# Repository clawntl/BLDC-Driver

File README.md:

# BLDC-Driver: a compact FOC driver board

BLDC-Driver is an integrated brushless motor driver built around an **STM32G431** microcontroller and a **TI DRV8316** three-phase gate driver with integrated MOSFETs. It runs field-oriented control (FOC) with [SimpleFOC](https://github.com/simplefoc) and takes current (torque) commands over CAN. It suits gimbal motors and small direct-drive wheels.

The board includes an optional **AS5048A** magnetic encoder on a break-away tab. With the tab removed, the board measures just **39 mm × 36 mm**.

## Features

| | |
|---|---|
| **MCU** | STM32G431CBU6 (Cortex-M4F, 170 MHz max, run at 160 MHz; CORDIC used for fast trig) |
| **Power stage** | DRV8316 with integrated FETs: 3 A continuous / 8 A peak, 6-PWM control over SPI |
| **Supply** | 5–35 V DC. The DRV8316 buck converter generates 5 V, and an XC6206 LDO generates 3.3 V |
| **Current sense** | DRV8316 integrated low-side current-sense amplifiers on all three phases |
| **Position sensor** | AS5048A 14-bit magnetic encoder (SPI1) on a break-away tab, or an external sensor via the SPI1 header |
| **Communication** | CAN via a TJA1051T/3 transceiver (FDCAN capable up to 5 Mbit/s; the firmware uses 1 Mbit/s classic CAN). Two JST-PH connectors allow daisy-chaining |
| **CAN termination** | Optional split 120 Ω termination, set with two jumpers |
| **Other I/O** | USB-C (CDC serial console + DFU flashing), SWD header, SPI3 header, user button, user LED, power LED |
| **Supply sensing** | 100 kΩ / 10 kΩ divider on VIN, read by the MCU (PA3) |
| **Mounting** | 4 × M2 holes, 33 mm × 30 mm spacing |

## Repository layout

| Path | Contents |
|---|---|
| [`Hardware/`](Hardware) | KiCad project for the v0.2 board (schematic, PCB, custom footprints and symbols) |
| [`Hardware/production/`](Hardware/production) | Fabrication outputs: Gerber zip, BOM and pick-and-place files (JLCPCB/LCSC part numbers) |
| [`schematic_v0.2.pdf`](schematic_v0.2.pdf) | PDF export of the schematic |
| [`Firmware/`](Firmware) | PlatformIO firmware: the CAN motor driver and a bench-test build |
| [`Images/`](Images) | Pinout diagram |
| [`docs/`](docs) | Detailed documentation (see below) |

## Documentation

- **[Hardware guide](docs/hardware.md)**: pin mapping, connectors, jumpers, buttons, LEDs and manufacturing notes.
- **[Firmware guide](docs/firmware.md)**: building, flashing, first-time configuration, the serial console, tuning parameters and the bench-test firmware.
- **[Test routines](docs/test-routines.md)**: step-by-step bench testing of a board, motor and encoder with the `motor_test` firmware, with expected readings and troubleshooting.
- **[CAN protocol](docs/can-protocol.md)**: message IDs, frame formats, status and error codes, plus an example host program.

## Quick start

1. **Install [PlatformIO](https://platformio.org/)** (the VS Code extension or the CLI).
2. **Put the board in DFU mode.** Hold **BOOT**, plug in USB-C (or tap **RST**), then release **BOOT**. On a board that's already running the firmware, you can type `dfu` in the serial console instead.
3. **Build and flash** from the `Firmware/` directory:
   ```bash
   cd Firmware
   ```
   ```bash
   pio run -e driver -t upload
   ```
4. **Configure the board** over USB serial. The board boots unconfigured, with CAN disabled:
   ```bash
   pio device monitor
   ```
   Then type:
   ```text
   set side left      # or: set side right  (selects the CAN IDs)
   set invert off     # optional: flip the sign of commands/telemetry for a mirrored motor
   save               # writes to flash and reboots
   ```
5. **Drive it over CAN** at 1 Mbit/s:
   - Send `0x10` to the board's command ID (`0x021` left / `0x022` right) to align and start FOC.
   - Wait for the `[0x10][1.0f]` reply.
   - Stream target currents in amps as two big-endian floats on ID `0x020` at least every 100 ms.

   See [docs/can-protocol.md](docs/can-protocol.md) for the full protocol.

> [!CAUTION]
> Test new motors with the wheels off the ground and a current-limited supply. The `motor_test` bench firmware ([docs/firmware.md](docs/firmware.md#bench-test-firmware-motor_test)) checks the encoder, power stage and current sense step by step before you run closed-loop control.

## Status

This is hardware revision **v0.2**. The firmware's default motor parameters (11 pole pairs, 2 A current limit, 10 V voltage limit) live in [`Firmware/include/motor_config.h`](Firmware/include/motor_config.h). Change them to match your motor.

## License

This project is shared under the terms of the [GNU Affero General Public License Version 3](https://choosealicense.com/licenses/agpl-3.0/) as published by the Free Software Foundation.

The bundled [`ACANFD_STM32_G431`](Firmware/lib/ACANFD_STM32_G431) library is a stripped-down fork of Pierre Molinaro's [ACANFD-STM32](https://github.com/pierremolinaro/acanfd-stm32) and keeps its own MIT license.

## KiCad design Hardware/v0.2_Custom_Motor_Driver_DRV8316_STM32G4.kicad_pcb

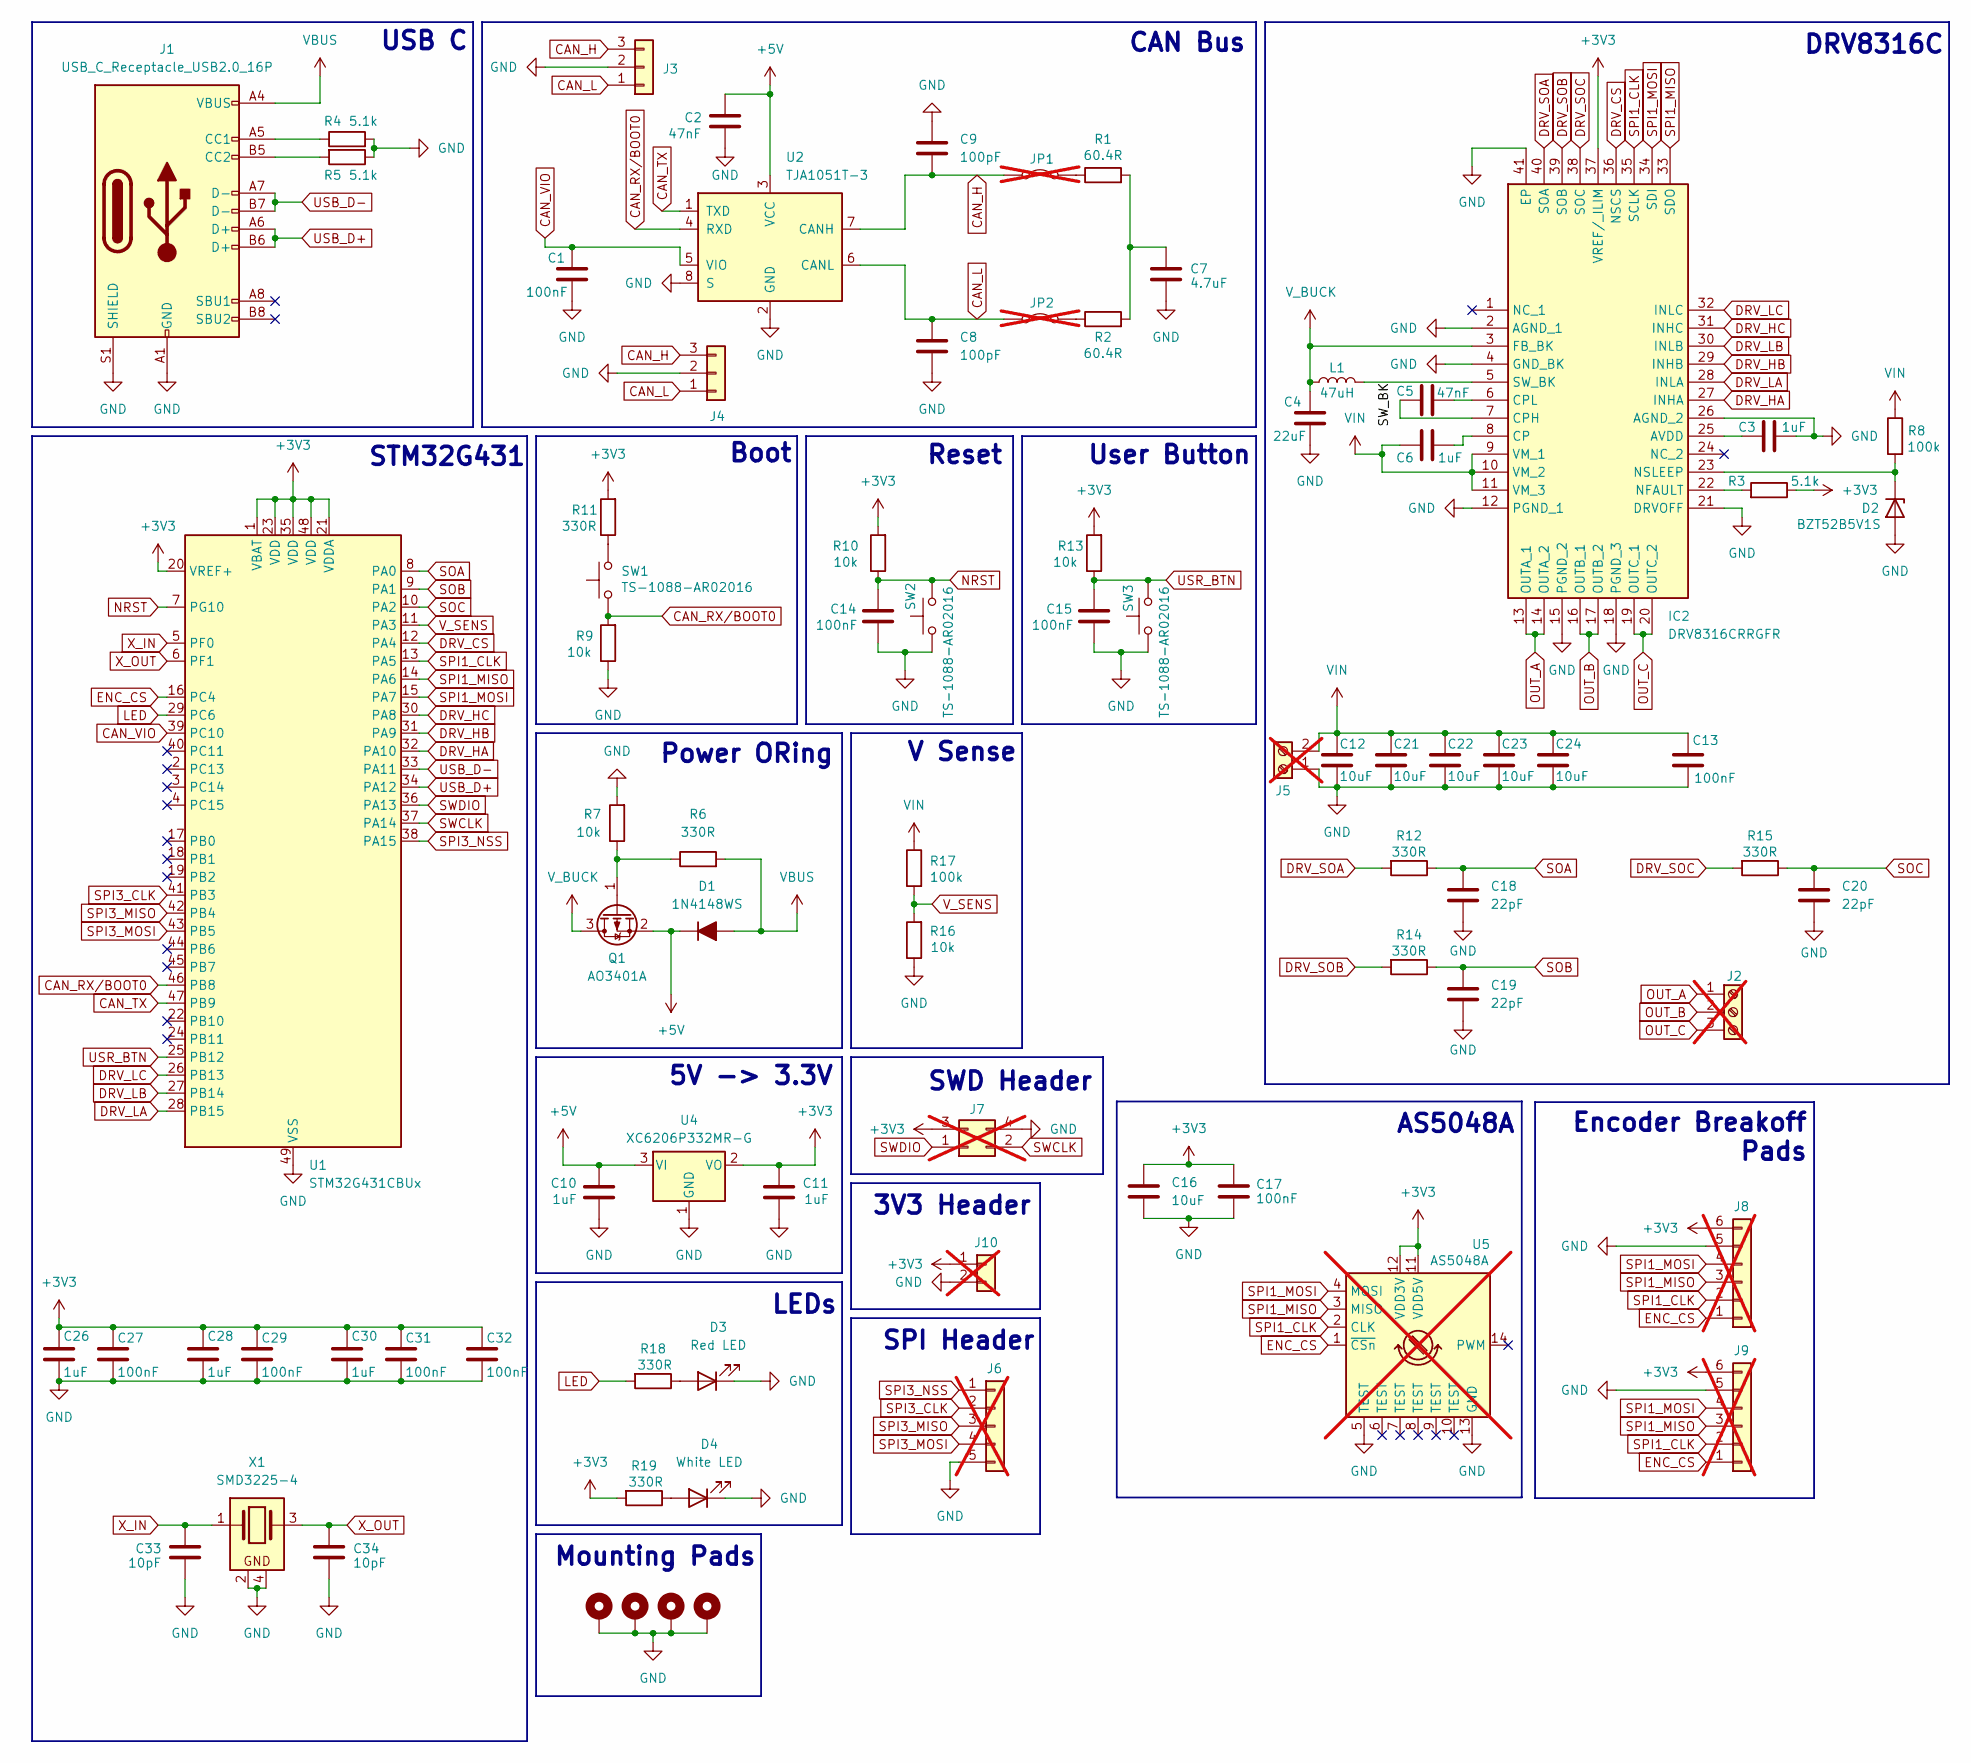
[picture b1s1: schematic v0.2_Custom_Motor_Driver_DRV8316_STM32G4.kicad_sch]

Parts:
C1, C13, C14, C15, C17, C27, C29, C31, C32: 100nF; C_0402_1005Metric; LCSC C307331
C2, C5: 47nF; C_0603_1608Metric; LCSC C1622
C3, C6, C10, C11, C26, C28, C30: 1uF; C_0402_1005Metric; LCSC C52923
C4: 22uF; C_0603_1608Metric; LCSC C59461
C7: 4.7uF; C_0805_2012Metric; LCSC C1779
C8, C9: 100pF; C_0402_1005Metric; LCSC C1546
C12, C21, C22, C23, C24: 10uF; C_0805_2012Metric; LCSC C440198
C16: 10uF; C_0603_1608Metric; LCSC C96446
C18, C19, C20: 22pF; C_0402_1005Metric; LCSC C1555
C33, C34: 10pF; C_0402_1005Metric; LCSC C32949
D1: 1N4148WS; D_SOD-323; LCSC C2128
D2: BZT52B5V1S; D_SOD-323_Zener; LCSC C19077434
D3: Red LED; LED_0603_1608Metric; LCSC C2286
D4: White LED; LED_0603_1608Metric; LCSC C2290
H1, H2, H3, H4: MountingHole_Pad; MountingHole_2.2mm_M2_Pad_Via
IC2: DRV8316CRRGFR; QFN50P500X700X100-41N-D; LCSC C5447274
J1: USB_C_Receptacle_USB2.0_16P; USB_C_Receptacle_GCT_USB4105-xx-A_16P_TopMnt_Horizontal; LCSC C393939
J2: Screw_Terminal_01x03; TerminalBlock_Xinya_XY308-2.54-3P_1x03_P2.54mm_Horizontal; not fitted
J3, J4: Conn_01x03; JST_PH_S3B-PH-K_1x03_P2.00mm_Horizontal; LCSC C157929
J5: Screw_Terminal_01x02; TerminalBlock_MaiXu_MX126-5.0-02P_1x02_P5.00mm; LCSC C3018698; not fitted
J6: Conn_01x05; PinHeader_1x05_P2.54mm_Vertical; not fitted
J7: Conn_02x02_Odd_Even; DebugHeader2x02_P1.27mm; not fitted
J8, J9: Conn_01x06; JST_PH_S6B-PH-K_1x06_P2.00mm_Horizontal Breakoff; not fitted
J10: Conn_01x02; PinHeader_1x02_P2.54mm_Vertical SLIM; not fitted
JP1, JP2: Jumper_2_Bridged; PinHeader_1x02_P2.54mm_Vertical; not fitted
L1: 47uH; L_Changjiang_FNR3015S; LCSC C96151
Q1: AO3401A; SOT-23; LCSC C15127
R1, R2: 60.4R; R_0805_2012Metric; LCSC C72998
R3, R4, R5: 5.1k; R_0402_1005Metric; LCSC C25905
R6, R11, R12, R14, R15, R18, R19: 330R; R_0402_1005Metric; LCSC C25104
R7, R9, R10, R13, R16: 10k; R_0402_1005Metric; LCSC C25744
R8, R17: 100k; R_0402_1005Metric; LCSC C25741
SW1, SW2, SW3: TS-1088-AR02016; LCSC C720477
U1: STM32G431CBUx; QFN-48-1EP_7x7mm_P0.5mm_EP5.6x5.6mm; LCSC C529356
U2: TJA1051T-3; SOIC-8_3.9x4.9mm_P1.27mm; LCSC C38695
U4: XC6206P332MR-G; SOT-23-3; LCSC C5446
U5: AS5048A; TSSOP-14_4.4x5mm_P0.65mm; not fitted
X1: SMD3225-4; Crystal_SMD_3225-4Pin_3.2x2.5mm; LCSC C13738

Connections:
+3V3: C11.2, C16.1, C17.1, C26.1, C27.1, C28.1, C29.1, C30.1, C31.1, C32.1, IC2.37 (VREF/_ILIM), J7.3, J8.6, J9.6, J10.1, R3.2, R10.2, R11.2, R13.2, R19.2, U1.1 (VBAT), U1.20 (VREF+), U1.21 (VDDA), U1.23 (VDD), U1.35 (VDD), U1.48 (VDD), U4.2 (VO), U5.11 (VDD5V), U5.12 (VDD3V)
+5V: C2.1, C10.2, D1.1 (K), Q1.2 (S), U2.3 (VCC), U4.3 (VI)
/SW_BK: IC2.5 (SW_BK), L1.2
CAN_H: C9.2, J3.3, J4.3, JP1.1 (A), U2.7 (CANH)
CAN_L: C8.1, J3.1, J4.1, JP2.1 (A), U2.6 (CANL)
CAN_RX/BOOT0: R9.2, SW1.1, U1.46 (PB8), U2.4 (RXD)
CAN_TX: U1.47 (PB9), U2.1 (TXD)
CAN_VIO: C1.1, U1.39 (PC10), U2.5 (VIO)
DRV_CS: IC2.36 (NSCS), U1.12 (PA4)
DRV_HA: IC2.27 (INHA), U1.32 (PA10)
DRV_HB: IC2.29 (INHB), U1.31 (PA9)
DRV_HC: IC2.31 (INHC), U1.30 (PA8)
DRV_LA: IC2.28 (INLA), U1.28 (PB15)
DRV_LB: IC2.30 (INLB), U1.27 (PB14)
DRV_LC: IC2.32 (INLC), U1.26 (PB13)
DRV_SOA: IC2.40 (SOA), R12.2
DRV_SOB: IC2.39 (SOB), R14.2
DRV_SOC: IC2.38 (SOC), R15.2
ENC_CS: J8.1, J9.1, U1.16 (PC4), U5.1 (~CSn)
GND: C1.2, C2.2, C3.2, C4.2, C7.2, C8.2, C9.1, C10.1, C11.1, C12.2, C13.2, C14.2, C15.2, C16.2, C17.2, C18.2, C19.2, C20.2, C21.2, C22.2, C23.2, C24.2, C26.2, C27.2, C28.2, C29.2, C30.2, C31.2, C32.2, C33.2, C34.2, D2.2 (A), D3.1 (K), D4.1 (K), H1.1, H2.1, H3.1, H4.1, IC2.2 (AGND_1), IC2.4 (GND_BK), IC2.12 (PGND_1), IC2.15 (PGND_2), IC2.18 (PGND_3), IC2.21 (DRVOFF), IC2.26 (AGND_2), IC2.41 (EP), J1.A1 (GND), J1.A12 (GND), J1.B1 (GND), J1.B12 (GND), J1.S1 (SHIELD), J3.2, J4.2, J5.1, J6.5, J7.4, J8.5, J9.5, J10.2, R4.2, R5.1, R7.2, R9.1, R16.1, SW2.1, SW3.1, U1.49 (VSS), U2.2 (GND), U2.8 (S), U4.1 (GND), U5.5 (TEST), U5.13 (GND), X1.2, X1.4
LED: R18.2, U1.29 (PC6)
NRST: C14.1, R10.1, SW2.2, U1.7 (PG10)
unnamed: C7.1, R1.2, R2.2
unnamed: D2.1 (K), IC2.23 (NSLEEP), R8.1
unnamed: D3.2 (A), R18.1
unnamed: D4.2 (A), R19.1
unnamed: C3.1, IC2.25 (AVDD)
unnamed: C6.2, IC2.8 (CP)
unnamed: C5.1, IC2.7 (CPH)
unnamed: C5.2, IC2.6 (CPL)
unnamed: IC2.22 (NFAULT), R3.1
unnamed: J1.A5 (CC1), R4.1
unnamed: J1.B5 (CC2), R5.2
unnamed: JP1.2 (B), R1.1
unnamed: JP2.2 (B), R2.1
unnamed: Q1.1 (G), R6.1, R7.1
unnamed: R11.1, SW1.2
OUT_A: IC2.13 (OUTA_1), IC2.14 (OUTA_2), J2.1
OUT_B: IC2.16 (OUTB_1), IC2.17 (OUTB_2), J2.2
OUT_C: IC2.19 (OUTC_1), IC2.20 (OUTC_2), J2.3
SOA: C18.1, R12.1, U1.8 (PA0)
SOB: C19.1, R14.1, U1.9 (PA1)
SOC: C20.1, R15.1, U1.10 (PA2)
SPI1_CLK: IC2.35 (SCLK), J8.2, J9.2, U1.13 (PA5), U5.2 (CLK)
SPI1_MISO: IC2.33 (SDO), J8.3, J9.3, U1.14 (PA6), U5.3 (MISO)
SPI1_MOSI: IC2.34 (SDI), J8.4, J9.4, U1.15 (PA7), U5.4 (MOSI)
SPI3_CLK: J6.2, U1.41 (PB3)
SPI3_MISO: J6.3, U1.42 (PB4)
SPI3_MOSI: J6.4, U1.43 (PB5)
SPI3_NSS: J6.1, U1.38 (PA15)
SWCLK: J7.2, U1.37 (PA14)
SWDIO: J7.1, U1.36 (PA13)
USB_D+: J1.A6 (D+), J1.B6 (D+), U1.34 (PA12)
USB_D-: J1.A7 (D-), J1.B7 (D-), U1.33 (PA11)
USR_BTN: C15.1, R13.1, SW3.2, U1.25 (PB12)
VBUS: D1.2 (A), J1.A4 (VBUS), J1.A9 (VBUS), J1.B4 (VBUS), J1.B9 (VBUS), R6.2
VIN: C6.1, C12.1, C13.1, C21.1, C22.1, C23.1, C24.1, IC2.9 (VM_1), IC2.10 (VM_2), IC2.11 (VM_3), J5.2, R8.2, R17.2
V_BUCK: C4.1, IC2.3 (FB_BK), L1.1, Q1.3 (D)
V_SENS: R16.2, R17.1, U1.11 (PA3)
X_IN: C33.1, U1.5 (PF0), X1.1
X_OUT: C34.1, U1.6 (PF1), X1.3

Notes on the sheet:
Power ORing
LEDs
5V -> 3.3V
V Sense
USB C
AS5048A
SWD Header
CAN Bus
SPI Header
STM32G431
Encoder Breakoff Pads
DRV8316C
Reset
3V3 Header
Mounting Pads
User Button
Boot

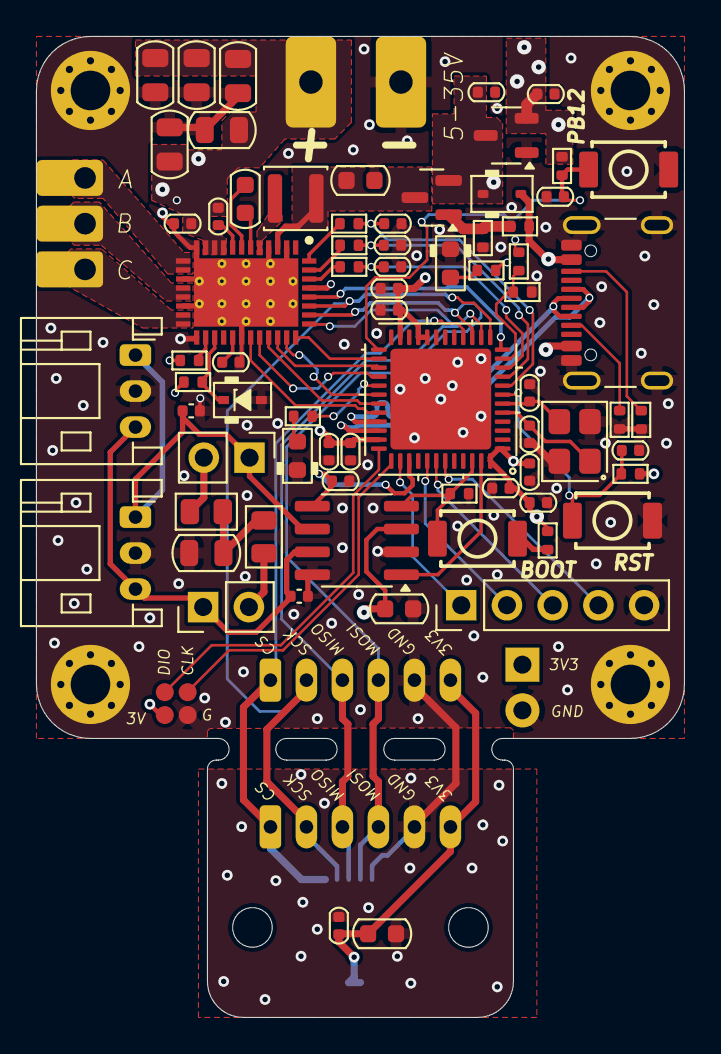
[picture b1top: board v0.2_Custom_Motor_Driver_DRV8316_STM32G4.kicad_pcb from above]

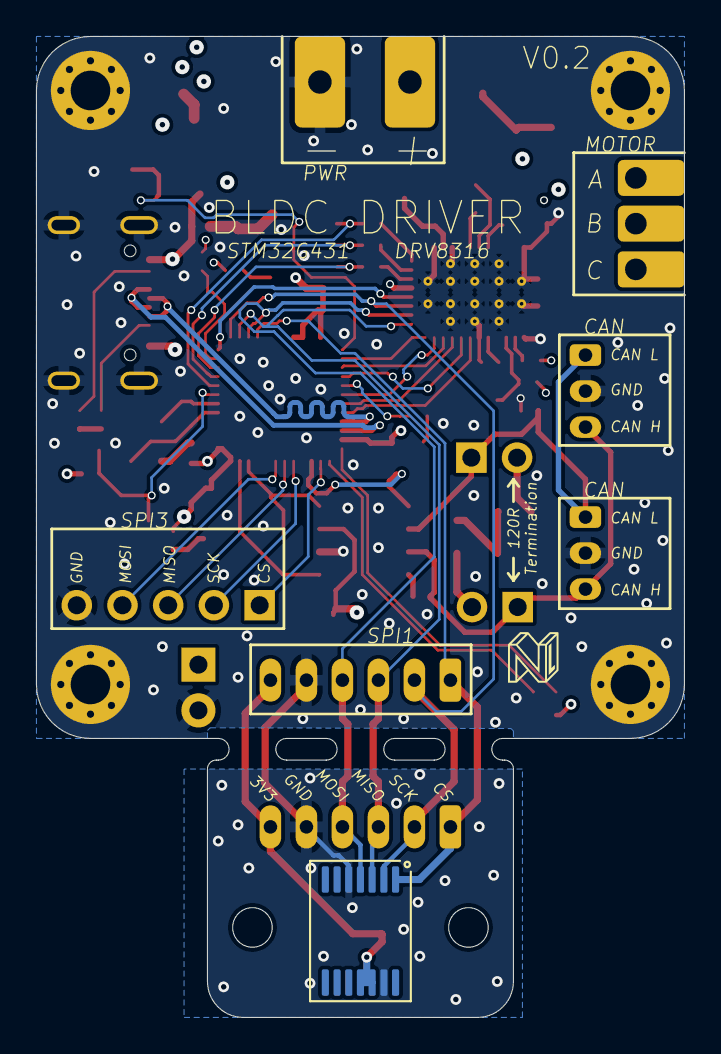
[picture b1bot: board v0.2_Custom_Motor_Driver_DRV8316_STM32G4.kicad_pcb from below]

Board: 4 copper layers, 36.0 x 54.5 mm, 83 parts (2 on the bottom side), 61 nets.

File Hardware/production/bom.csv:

Designator,Footprint,Quantity,Value,LCSC Part #
"C1, C13, C14, C15, C17, C27, C29, C31, C32",0402,9,100nF,C307331
"C10, C11, C26, C28, C3, C30, C6",0402,7,1uF,C52923
"C12, C21, C22, C23, C24",0805,5,10uF,C440198
C16,0603,1,10uF,C96446
"C18, C19, C20",0402,3,22pF,C1555
"C2, C5",0603,2,47nF,C1622
"C33, C34",0402,2,10pF,C32949
C4,0603,1,22uF,C59461
C7,0805,1,4.7uF,C1779
"C8, C9",0402,2,100pF,C1546
D1,D_SOD-323,1,1N4148WS,C2128
D2,D_SOD-323_Zener,1,BZT52B5V1S,C19077434
D3,0603,1,Red LED,C2286
D4,0603,1,White LED,C2290
IC2,QFN50P500X700X100-41N-D,1,DRV8316CRRGFR,C5447274
J1,USB_C_Receptacle_GCT_USB4105-xx-A_16P_TopMnt_Horizontal,1,USB_C_Receptacle_USB2.0_16P,C393939
"J3, J4",JST_PH_S3B-PH-K_1x03_P2.00mm_Horizontal,2,Conn_01x03,C157929
L1,L_Changjiang_FNR3015S,1,47uH,C96151
Q1,SOT-23,1,AO3401A,C15127
"R1, R2",0805,2,60.4R,C72998
"R10, R13, R16, R7, R9",0402,5,10k,C25744
"R11, R12, R14, R15, R18, R19, R6",0402,7,330R,C25104
"R17, R8",0402,2,100k,C25741
"R3, R4, R5",0402,3,5.1k,C25905
"SW1, SW2, SW3",TS-1088-AR02016,3,TS-1088-AR02016,C720477
U1,QFN-48-1EP_7x7mm_P0.5mm_EP5.6x5.6mm,1,STM32G431CBUx,C529356
U2,SOIC-8_3.9x4.9mm_P1.27mm,1,TJA1051T-3,C38695
U4,SOT-23-3,1,XC6206P332MR-G,C5446
X1,Crystal_SMD_3225-4Pin_3.2x2.5mm,1,SMD3225-4,C13738

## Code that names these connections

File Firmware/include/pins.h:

#pragma once

// Board pin mapping for the custom STM32G431CBU6 motor driver board.

// The generic G431CB variant defines LED_BUILTIN as "not defined"; replace it.
#undef LED_BUILTIN
#define LED_BUILTIN PC6

#define DFU_BUTTON PB12 // pull low (button to GND) to force the USB DFU bootloader

#define SPI1_SCK   PA5
#define SPI1_MISO  PA6
#define SPI1_MOSI  PA7
#define DRV_CS     PA4
#define ENC_CS     PC4

#define CAN_EN  PC10 // CAN transceiver enable: HIGH = on

// FDCAN1 RX is on PB8, which is also BOOT0 (10k pull-down + BOOT button to
// 3V3). See softwareReset() in dfu.cpp for why that matters.
#define CAN_RX_BOOT0 PB8

#define PHA_H   PA10
#define PHA_L   PB15

#define PHB_H   PA9
#define PHB_L   PB14

#define PHC_H   PA8
#define PHC_L   PB13

#define SO_A    PA0
#define SO_B    PA1
#define SO_C    PA2

#define V_SENS  PA3 // VIN / 11 via R17 100k / R16 10k divider

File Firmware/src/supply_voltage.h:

#pragma once

#include <cstdint>

// Supply (VIN) measurement via the on-board V_SENS divider:
//   VIN -> R17 100k -> PA3 (V_SENS) -> R16 10k -> GND   =>  V_PA3 = VIN / 11
//
// !! Only call these BEFORE current_sense.init() !!
// STM32duino's analogRead() initialises the ADC for each read and then
// HAL_ADC_DeInit()s it. PA3 is on ADC1 together with the SOA/SOB/SOC
// current-sense pins, so an analogRead() after SimpleFOC has configured the
// ADC for low-side current sensing would silently break current sensing.

// Averaged supply voltage in volts.
float readSupplyVoltage(uint16_t samples = 64);

// Measures VIN and returns it if it is within [SUPPLY_VOLTAGE_MIN,
// SUPPLY_VOLTAGE_MAX]; otherwise prints a warning and returns the fallback
// MOTOR_VOLTAGE_POWER_SUPPLY from motor_config.h.
float measuredSupplyVoltageOrDefault();

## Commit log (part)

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2025-07-08 Add PCB files
2025-07-08 Added BLDC Driver Pinout Diagram
2025-07-08 Fixed BLDC Driver Pinout Diagram
2025-07-08 Uploaded BLDC Driver Pinout Diagram
2025-11-12 Added example showing useage
